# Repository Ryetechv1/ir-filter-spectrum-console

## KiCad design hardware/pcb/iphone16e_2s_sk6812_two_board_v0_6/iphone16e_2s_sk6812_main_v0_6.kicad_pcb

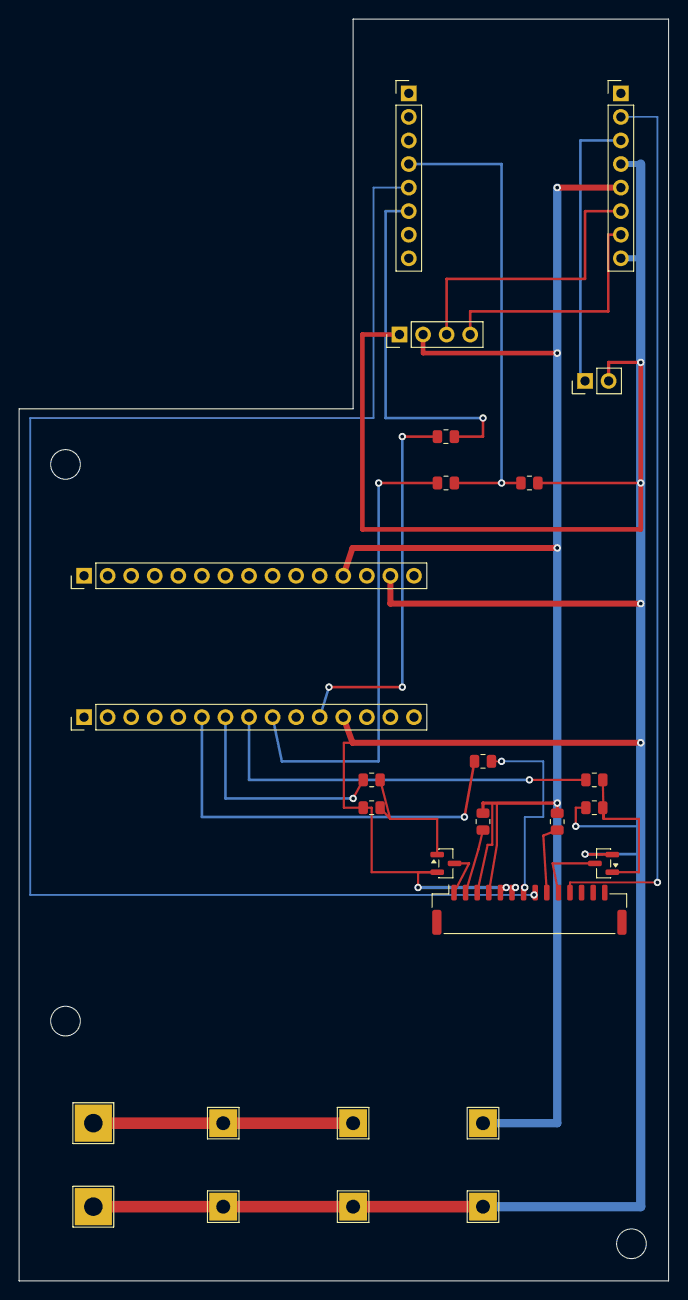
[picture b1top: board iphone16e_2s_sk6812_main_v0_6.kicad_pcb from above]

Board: 2 copper layers, 70.0 x 136.0 mm, 30 parts (0 on the bottom side), 22 nets.

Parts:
H1, H2, H3: mount; MountingHole_3.2mm_M3
J1: ESP32-CAM LEFT; PinHeader_1x08_P2.54mm_Vertical
J2: ESP32-CAM RIGHT; PinHeader_1x08_P2.54mm_Vertical
J3: USB-UART; PinHeader_1x04_P2.54mm_Vertical
J4: NANO LEFT ROW; PinHeader_1x15_P2.54mm_Vertical
J5: NANO RIGHT ROW; PinHeader_1x15_P2.54mm_Vertical
J8: LED HEAD JST-GH; JST_GH_SM14B-GHS-TB_1x14-1MP_P1.25mm_Horizontal
JP1: BOOT; PinHeader_1x02_P2.54mm_Vertical
P1: 2S PACK +; TestPoint_THTPad_4.0x4.0mm_Drill2.0mm
P2: PACK -; TestPoint_THTPad_4.0x4.0mm_Drill2.0mm
P3: 2S CHG +; TestPoint_THTPad_3.0x3.0mm_Drill1.5mm
P4: 2S CHG -; TestPoint_THTPad_3.0x3.0mm_Drill1.5mm
P5: BUCK IN +; TestPoint_THTPad_3.0x3.0mm_Drill1.5mm
P6: BUCK IN -; TestPoint_THTPad_3.0x3.0mm_Drill1.5mm
P7: 5V SYS +; TestPoint_THTPad_3.0x3.0mm_Drill1.5mm
P8: 5V SYS -; TestPoint_THTPad_3.0x3.0mm_Drill1.5mm
Q1: AO3400A IR; SOT-23
Q2: AO3400A UVA; SOT-23
R1: 100R 0.25W; R_0805_2012Metric
R2, R5: 150R; R_0805_2012Metric
R3, R6: 100k; R_0805_2012Metric
R4: 68R 0.25W; R_0805_2012Metric
R7: 330R; R_0805_2012Metric
R8: 1k; R_0805_2012Metric
R9: 2k; R_0805_2012Metric
R10: 470R; R_0805_2012Metric

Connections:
+5V_SYS: J2.5, J3.2, J4.12, J8.3, J8.4, P7.1, R1.1, R4.1
ESP_GPIO13_RX: J1.4, R8.2, R9.1
ESP_GPIO14_TX: J1.6, R10.2
ESP_GPIO15_GLASS_SDA: J1.5, J8.8
ESP_GPIO16_GLASS_SCL: J2.2, J8.11
ESP_IO0_BOOT: J2.3, JP1.1
ESP_U0R_PROG: J2.6, J3.3
ESP_U0T_PROG: J2.7, J3.4
GND: J2.4, J2.8, J3.1, J4.14, J5.12, J8.5, J8.6, JP1.2, P2.1, P4.1, P6.1, P8.1, Q1.2, Q2.2, R3.1, R6.1, R9.2
IR_ANODE: J8.9, R1.2
IR_GATE: Q1.1, R2.2, R3.2
IR_NEG: J8.10, Q1.3
NANO_D2_RX: J5.11, R10.1
NANO_D4_TX: J5.9, R8.1
NANO_D5_IR_PWM: J5.8, R2.1
NANO_D6_UVA_PWM: J5.7, R5.1
NANO_D7_SK6812_DATA: J5.6, R7.1
SK6812_DIN_1: J8.7, R7.2
UVA_ANODE: J8.2, R4.2
UVA_GATE: Q2.1, R5.2, R6.2
UVA_NEG: J8.1, Q2.3
VBAT_2S: P1.1, P3.1, P5.1

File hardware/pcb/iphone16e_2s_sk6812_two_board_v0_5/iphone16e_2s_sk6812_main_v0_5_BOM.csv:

Comment,Designator,Footprint,Quantity,Layer,Assembly Type,LCSC Part #,Notes
ESP32-CAM LEFT,J1,PinHeader_1x08_P2.54mm_Vertical,1,Top,THT,,"ESP32-CAM left 1x08 socket/header, hand solder unless fab supports THT assembly"
ESP32-CAM RIGHT,J2,PinHeader_1x08_P2.54mm_Vertical,1,Top,THT,,"ESP32-CAM right 1x08 socket/header, hand solder unless fab supports THT assembly"
USB-UART,J3,PinHeader_1x04_P2.54mm_Vertical,1,Top,THT,,"USB-UART upload header: GND, 5V, adapter TX, adapter RX"
NANO LEFT ROW,J4,PinHeader_1x15_P2.54mm_Vertical,1,Top,THT,,"Arduino Nano left socket/header, hand solder unless fab supports THT assembly"
NANO RIGHT ROW,J5,PinHeader_1x15_P2.54mm_Vertical,1,Top,THT,,"Arduino Nano right socket/header, hand solder unless fab supports THT assembly"
LED HEAD FFC,J8,Molex_200528-0140_1x14-1MP_P1.00mm_Horizontal,1,Top,SMT,,14-pin 1.0 mm FFC/FPC connector to LED head board
BOOT,JP1,PinHeader_1x02_P2.54mm_Vertical,1,Top,THT,,ESP32-CAM boot jumper; short IO0 to GND only while uploading
AO3400A IR,Q1,SOT-23,1,Top,SMT,,Logic-level NMOS for IR LED low-side PWM
AO3400A UVA,Q2,SOT-23,1,Top,SMT,,Logic-level NMOS for UVA LED low-side PWM
100R 0.25W,R1,R_0805_2012Metric,1,Top,SMT,,"IR current limit from 5V, about 35 mA with 1.5V Vf"
150R,"R2,R5",R_0805_2012Metric,2,Top,SMT,,
100k,"R3,R6",R_0805_2012Metric,2,Top,SMT,,
68R 0.25W,R4,R_0805_2012Metric,1,Top,SMT,,"UVA current limit from 5V, about 21 mA with 3.6V Vf"
330R,R7,R_0805_2012Metric,1,Top,SMT,,SK6812 RGBW data series resistor before FFC cable
1k,R8,R_0805_2012Metric,1,Top,SMT,,Nano D4 to ESP32-CAM RX divider high side
2k,R9,R_0805_2012Metric,1,Top,SMT,,Nano D4 to ESP32-CAM RX divider low side
470R,R10,R_0805_2012Metric,1,Top,SMT,,ESP32-CAM GPIO14 to Nano D2 series resistor

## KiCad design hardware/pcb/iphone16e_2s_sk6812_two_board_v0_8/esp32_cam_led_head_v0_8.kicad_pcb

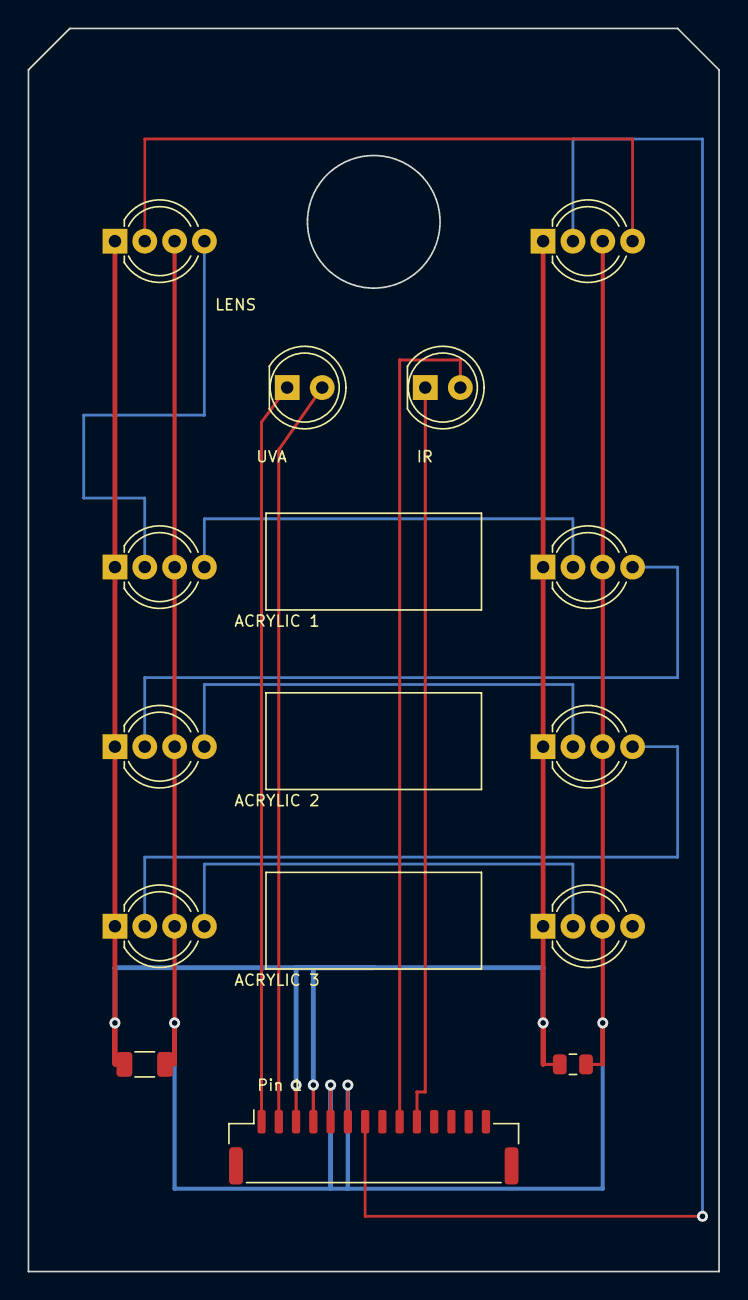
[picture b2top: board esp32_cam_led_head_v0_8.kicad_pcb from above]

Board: 2 copper layers, 50.0 x 90.0 mm, 13 parts (0 on the bottom side), 14 nets.

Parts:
C1: 47uF-100uF; C_1206_3216Metric
C2: 0.1uF; C_0805_2012Metric
D1: 950nm IR; LED_D5.0mm_IRBlack
D2: 375nm UVA; LED_D5.0mm_Clear
D3: RGBW 1 RIGHT; LED_D5.0mm-4_RGB_Wide_Pins
D4: RGBW 2 LEFT; LED_D5.0mm-4_RGB_Wide_Pins
D5: ACRYLIC 1 LEFT; LED_D5.0mm-4_RGB_Wide_Pins
D6: ACRYLIC 1 RIGHT; LED_D5.0mm-4_RGB_Wide_Pins
D7: ACRYLIC 2 LEFT; LED_D5.0mm-4_RGB_Wide_Pins
D8: ACRYLIC 2 RIGHT; LED_D5.0mm-4_RGB_Wide_Pins
D9: ACRYLIC 3 LEFT; LED_D5.0mm-4_RGB_Wide_Pins
D10: ACRYLIC 3 RIGHT; LED_D5.0mm-4_RGB_Wide_Pins
J1: 14P JST-GH TO MAIN; JST_GH_SM14B-GHS-TB_1x14-1MP_P1.25mm_Horizontal

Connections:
+5V_LED: C1.1, C2.1, D3.1, D4.1, D5.1, D6.1, D7.1, D8.1, D9.1, D10.1, J1.3, J1.4
GND: C1.2, C2.2, D3.3, D4.3, D5.3, D6.3, D7.3, D8.3, D9.3, D10.3, J1.5, J1.6
IR_ANODE: D1.2, J1.9
IR_NEG: D1.1, J1.10
SK6812_1_TO_2: D3.4, D4.2
SK6812_2_TO_3: D4.4, D5.2
SK6812_3_TO_4: D5.4, D6.2
SK6812_4_TO_5: D6.4, D7.2
SK6812_5_TO_6: D7.4, D8.2
SK6812_6_TO_7: D8.4, D9.2
SK6812_7_TO_8: D9.4, D10.2
SK6812_DIN_1: D3.2, J1.7
UVA_ANODE: D2.2, J1.2
UVA_NEG: D2.1, J1.1

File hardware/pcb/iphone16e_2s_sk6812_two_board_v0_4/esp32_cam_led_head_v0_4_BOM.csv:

Comment,Designator,Footprint,Quantity,Layer,Assembly Type,LCSC Part #,Notes
47uF-100uF,C1,C_1206_3216Metric,1,Top,SMT,,Bulk capacitor across regulated 5V LED rail
0.1uF,C2,C_0805_2012Metric,1,Top,SMT,,Local LED rail bypass capacitor
950nm IR,D1,LED_D5.0mm_IRBlack,1,Top,THT,,"950 nm 5 mm IR LED, verify vendor polarity before assembly"
375nm UVA,D2,LED_D5.0mm_Clear,1,Top,THT,,"375 nm 5 mm UVA LED, verify vendor polarity and use UV shielding"
RGBW 1 RIGHT,D3,LED_D5.0mm-4_RGB_Wide_Pins,1,Top,THT,,SK6812 RGBW 5 mm LED 1 right of lens; verify exact vendor pinout
RGBW 2 LEFT,D4,LED_D5.0mm-4_RGB_Wide_Pins,1,Top,THT,,SK6812 RGBW 5 mm LED 2 left of lens; verify exact vendor pinout
14P FFC TO MAIN,J1,Molex_200528-0140_1x14-1MP_P1.00mm_Horizontal,1,Top,SMT,,"14-pin 1.0 mm FFC/FPC connector, Molex 200528-0140 or compatible"

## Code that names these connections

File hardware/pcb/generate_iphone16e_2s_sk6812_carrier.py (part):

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        "+5V_LED",
        "LED_SW_GATE",
        "LED_EN_GATE",
        "ESP_GPIO13_RX",
        "ESP_GPIO14_TX",
        "ESP_U0R_PROG",
        "ESP_U0T_PROG",
        "ESP_IO0_BOOT",
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
    esp_l = load_fp("Connector_PinHeader_2.54mm", "PinHeader_1x08_P2.54mm_Vertical", "J1", "ESP32-CAM LEFT", 42.0, 8.0)
    esp_r = load_fp("Connector_PinHeader_2.54mm", "PinHeader_1x08_P2.54mm_Vertical", "J2", "ESP32-CAM RIGHT", 64.86, 8.0)
    set_net(esp_l, {"4": "ESP_GPIO13_RX", "6": "ESP_GPIO14_TX"}, nets)
    set_net(esp_r, {"3": "ESP_IO0_BOOT", "4": "GND", "5": "+5V_SYS", "6": "ESP_U0R_PROG", "7": "ESP_U0T_PROG", "8": "GND"}, nets)
    board.Add(esp_l)
    board.Add(esp_r)
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
    add_text(board, "D8 logical power in firmware", 38.0, 115.0, 0.8)

    r_tx_hi = add_res(board, nets, "R8", "1k", 46.0, 50.0, "NANO_D4_TX", "ESP_GPIO13_RX", 0)
    r_tx_lo = add_res(board, nets, "R9", "2k", 55.0, 50.0, "ESP_GPIO13_RX", "GND", 0)
    r_rx = add_res(board, nets, "R10", "470R", 46.0, 45.0, "NANO_D2_RX", "ESP_GPIO14_TX", 0)
    r_data = add_res(board, nets, "R7", "330R", 50.0, 80.0, "NANO_D7_SK6812_DATA", "SK6812_DIN_1", 0)
    r_ir_led = add_res(board, nets, "R1", "100R 0.25W", 58.0, 86.5, "+5V_SYS", "IR_ANODE", 270)
    r_uva_led = add_res(board, nets, "R4", "68R 0.25W", 50.0, 86.5, "+5V_SYS", "UVA_ANODE", 270)
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    route(board, nets, [via_d2_jump_b.GetPosition(), via_nano_d2.GetPosition()], "NANO_D2_RX", 0.28, pcbnew.B_Cu)
    route(board, nets, [via_nano_d2.GetPosition(), pad(r_rx, "1").GetPosition()], "NANO_D2_RX", 0.28, pcbnew.F_Cu)

    via_esp13 = add_via(board, nets, 52.0, 50.0, "ESP_GPIO13_RX")
    route(board, nets, [pad(r_tx_hi, "2").GetPosition(), via_esp13.GetPosition(), pad(r_tx_lo, "1").GetPosition()], "ESP_GPIO13_RX", 0.28, pcbnew.F_Cu)
    route(board, nets, [via_esp13.GetPosition(), (52.0, 15.62), pad(esp_l, "4").GetPosition()], "ESP_GPIO13_RX", 0.28, pcbnew.B_Cu)
    via_r9_gnd = add_via(board, nets, 67.0, 50.0, "GND")
    route(board, nets, [pad(r_tx_lo, "2").GetPosition(), via_r9_gnd.GetPosition()], "GND", 0.28, pcbnew.F_Cu)
    via_esp14 = add_via(board, nets, 50.0, 43.0, "ESP_GPIO14_TX")
    route(board, nets, [pad(esp_l, "6").GetPosition(), (39.5, 20.7), (39.5, 43.0), via_esp14.GetPosition()], "ESP_GPIO14_TX", 0.28, pcbnew.B_Cu)
    route(board, nets, [via_esp14.GetPosition(), (50.0, 45.0), pad(r_rx, "2").GetPosition()], "ESP_GPIO14_TX", 0.28, pcbnew.F_Cu)

    connect(board, nets, esp_r, "6", prog, "3", "ESP_U0R_PROG", 0.28, pcbnew.F_Cu, [(61.0, 20.7), (61.0, 28.0), (46.08, 28.0)])
    connect(board, nets, esp_r, "7", prog, "4", "ESP_U0T_PROG", 0.28, pcbnew.F_Cu, [(63.5, 23.24), (63.5, 31.5), (48.62, 31.5)])
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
